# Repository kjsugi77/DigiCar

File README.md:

## 構成フォルダ
- program/        ← 車両制御プログラム（C++）
- electronics/    ← 基板データ（KiCad / Gerber / 回路図PDF）
- 3d_print/       ← 3Dプリント用データ（STL）
- parts/          ← 部品表（BOM）

---

# DigiCar（デジカー）

DigiCar は、ミニ四駆サイズの学習用自動運転ミニカーです。  
プリント基板そのものがシャーシとなる独自構造を採用し、  
RumiCar をリスペクトした教育向けプラットフォームとして開発されています。

2025年8月30日の「デジもく会」にて正式発表されました。

---

## 特徴

- プリント基板がシャーシとして機能する独自構造
- 自動運転機能を搭載予定（ToF センサ対応）
- Bluetooth をメインとした無線通信
- 教育教材としての普及を目指した低コスト設計（想定金額 約5,000円）

---

## システム構成

DigiCar は **電気系・プログラム・機械系** の 3 要素で構成されています。

### ● 電気系
- マイコン：ESP32-WROOM-32E  
- モータードライバ：TB6612FNG（東芝）  
- 電圧レギュレータ：TC1262-3.3VDB05（Microchip）  
- USBシリアル変換：FT231XS（FTDI）  
- 通信方式：Bluetooth（メイン）、Wi-Fi（サブ）

### ● プログラム
- 使用言語：C++（Arduino IDE）

### ● 機械系
- ステアリング：SG-90 サーボモータ  
- 駆動モータ：マブチ FA-130  
- ギア・シャフト・タイヤ：タミヤ製を中心に構成  
- 3Dプリント部品：ギヤケース、ステアリング機構、電池ケース固定部品など

---

## 開発ストーリー

### 2020年〜：胎動（暗黒時代）
N氏による構想が始まるも、具体化せず停滞。

### 2024年2月：運命の再始動
デジもく会で H氏の「基板、作りませんか？」の一言から再燃。

### 2025年3〜5月：継承と本格始動
京都NTで試作モックを受領し、開発が本格化。

### 2025年8〜9月：公開とコミュニティ化
初発表で手応えを掴み、はんだ付け会や Discord 開設へ。

### 2025年10〜11月：危機と復活
通信不良・異常電流の問題を発見。配線ミスを特定し、改良基板で復活。

### 2026年2月〜現在：次のステージへ
サンプル3台を提供し、マニュアル操作アプリも完成。  
現在は ToF センサ搭載による自動運転へ挑戦中。

---

## コスト構成（概算：ToF センサ除く 約 4,000 円）

### 1. 電気・電子部品（約 1,500 円）
- ESP32-WROOM-32E：約 800 円  
- FT231XS：約 320 円  
- TB6612FNG：約 200 円  
- その他：基板、抵抗・コンデンサ類

### 2. 駆動・メカ部品（約 1,000 円強）
- SG-90 サーボ：650 円  
- ギヤ・シャフト・タイヤ類：約 400 円  
- 3Dプリント部品、ネジ類

### 3. 電源（約 1,000 円強）
- エネループライト（単4×4本）：約 1,000 円  
- 電池ボックス（スイッチ付）：100 円

### 4. その他
- 基板（JLCPCB）：約 100 円

---

## ライセンス

本リポジトリは **MIT License** のもとで公開されています。

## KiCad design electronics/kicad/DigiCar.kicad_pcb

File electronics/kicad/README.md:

# kicad フォルダについて

このフォルダには、DigiCar の基板設計に使用している KiCad プロジェクトの主要ファイルが含まれています。  
回路図（schematic）と PCB レイアウト（pcb）を編集する際に使用します。

## 含まれるファイル

- **DigiCar.kicad_pro**  
  KiCad プロジェクトファイルです。  
  このファイルを開くことで、回路図エディタと PCB エディタを利用できます。

- **DigiCar.kicad_sch**  
  DigiCar の回路図データです。  
  電気的な接続、部品構成、信号ラインなどを編集できます。

- **DigiCar.kicad_pcb**  
  DigiCar の基板レイアウトデータです。  
  部品配置、配線、基板形状などを編集できます。

## 使い方

1. KiCad を起動し、**DigiCar.kicad_pro** を開きます。  
2. 回路図（Schematic Editor）または基板レイアウト（PCB Editor）を編集できます。

# About the kicad folder

This folder contains the main KiCad project files used for designing the DigiCar PCB.  
These files are used when editing the schematic and PCB layout.

## Included Files

- **DigiCar.kicad_pro**  
  The KiCad project file.  
  Opening this file allows you to access both the schematic editor and the PCB editor.

- **DigiCar.kicad_sch**  
  The schematic file for DigiCar.  
  You can edit electrical connections, component configuration, and signal lines.

- **DigiCar.kicad_pcb**  
  The PCB layout file for DigiCar.  
  You can edit component placement, routing, and the board outline.

## How to Use

1. Launch KiCad and open **DigiCar.kicad_pro**.  
2. Edit the schematic (Schematic Editor) or the PCB layout (PCB Editor) as needed.

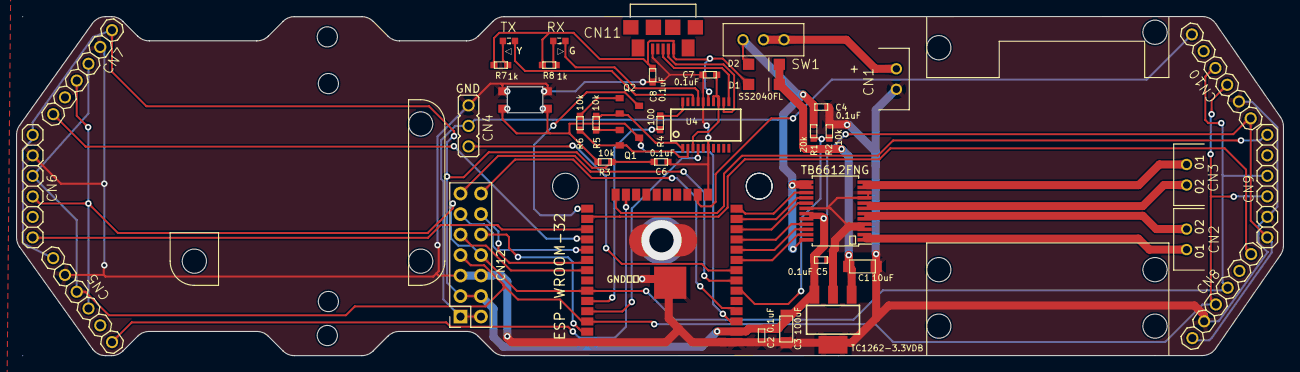
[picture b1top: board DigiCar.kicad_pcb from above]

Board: 2 copper layers, 157.0 x 42.0 mm, 40 parts (0 on the bottom side), 48 nets.

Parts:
C1: 10uF; CP3216
C2, C4, C5, C6, C7, C8: 0.1uF; CP1608
C3: 100uF; CP3216
CN1, CN2, CN3: EH-2
CN4: PINHD-1X3; CON_RC_SERVO
CN5, CN6, CN7, CN8, CN9, CN10: PINHD-1X6; 1X06
CN11: ZX62-B-5PA(11); CONN_ZX62-B-5PA(11)_HIR
CN12: Conn_02x07_Odd_Even; PinSocket_2x07_P2.54mm_Vertical
D1, D2: SS2040FL; SOD123
ESP-WROOM-32: ESP-WROOM-32
Q1, Q2: 2SC2712; SC59
R1: 20k; CP1608
R2, R3, R5, R6: 10k; CP1608
R4: 100; CP1608
R7, R8: 1k; CP1608
RX: GREEN; LED1608
SW1: SS-12SDP2; SLIDE-SW
SW2: SKRPACE010
TB6612FNG: TB6612FNG; SSOP-24_5.3x8.2mm_P0.65mm
TC1262-3.3VDB: TC1262-3.3VDB; SOT223
TX: YELLOW; LED1608
U4: FT231XS; SSOP20

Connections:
+3V3: C2.SMD1 (PIN1), C3.SMD1 (PIN1), C5.SMD1 (PIN1), C6.SMD1 (PIN1), CN5.1, CN6.1, CN7.1, CN8.1, CN9.1, CN10.1, CN12.3, CN12.4, ESP-WROOM-32.2 (3V3), R3.SMD2 (PIN2), TB6612FNG.19 (STBY), TB6612FNG.20 (VCC), TC1262-3.3VDB.3 (VO)
/BATT_CHECK: ESP-WROOM-32.6 (IO34), R1.SMD1 (PIN1), R2.SMD2 (PIN2)
/BOOT: ESP-WROOM-32.25 (IO0), Q2.C
/IO5_SS: CN12.11, ESP-WROOM-32.29 (IO5)
/IO18_SCK: CN12.12, ESP-WROOM-32.30 (IO18)
/IO19_MISO: CN12.9, ESP-WROOM-32.31 (IO19)
/IO23_MOSI: CN12.10, ESP-WROOM-32.37 (IO23)
/IO35: CN12.13, ESP-WROOM-32.7 (IO35)
/IO36: CN12.14, ESP-WROOM-32.4 (SENSOR_VP)
/MOTOR_A_IN1: ESP-WROOM-32.11 (IO26), TB6612FNG.21 (AIN1)
/MOTOR_A_IN2: ESP-WROOM-32.10 (IO25), TB6612FNG.22 (AIN2)
/MOTOR_B_IN1: ESP-WROOM-32.12 (IO27), TB6612FNG.17 (BIN1)
/MOTOR_B_IN2: ESP-WROOM-32.13 (IO14), TB6612FNG.16 (BIN2)
/MOTOR_PWM_A: ESP-WROOM-32.9 (IO33), TB6612FNG.23 (PWMA)
/MOTOR_PWM_B: ESP-WROOM-32.14 (IO12), TB6612FNG.15 (PWMB)
/RESET: ESP-WROOM-32.3 (EN), Q1.C, R3.SMD1 (PIN1), SW2.1, SW2.2
/RXD: ESP-WROOM-32.34 (RXD0), R4.SMD2 (PIN2)
/RX_LED: RX.C, U4.17 (CBUS1)
/SCL: CN5.3, CN6.3, CN7.3, CN8.3, CN9.3, CN10.3, CN12.7, ESP-WROOM-32.36 (IO22)
/SDA: CN5.4, CN6.4, CN7.4, CN8.4, CN9.4, CN10.4, CN12.8, ESP-WROOM-32.33 (IO21)
/SERVO_PWM: CN4.1, ESP-WROOM-32.8 (IO32)
/TOF_SHDN0: CN5.6, ESP-WROOM-32.23 (IO15)
/TOF_SHDN1: CN6.6, ESP-WROOM-32.27 (IO16)
/TOF_SHDN2: CN7.6, ESP-WROOM-32.28 (IO17)
/TOF_SHDN3: CN8.6, ESP-WROOM-32.26 (IO4)
/TOF_SHDN4: CN9.6, ESP-WROOM-32.24 (IO2)
/TOF_SHDN5: CN10.6, ESP-WROOM-32.16 (IO13)
/TXD: ESP-WROOM-32.35 (TXD0), U4.4 (RXD)
/TX_LED: TX.C, U4.18 (CBUS0)
GND: C1.SMD2 (PIN2), C2.SMD2 (PIN2), C3.SMD2 (PIN2), C4.SMD2 (PIN2), C5.SMD2 (PIN2), C6.SMD2 (PIN2), C7.SMD2 (PIN2), C8.SMD2 (PIN2), CN1.2, CN4.3, CN5.2, CN6.2, CN7.2, CN8.2, CN9.2, CN10.2, CN11.5, CN12.5, CN12.6, ESP-WROOM-32.1 (GND@1), ESP-WROOM-32.15 (GND@2), ESP-WROOM-32.38 (GND@3), ESP-WROOM-32.GND (GND@4), R2.SMD1 (PIN1), SW2.3, SW2.4, TB6612FNG.3 (PGND1), TB6612FNG.4 (PGND1), TB6612FNG.9 (PGND2), TB6612FNG.10 (PGND2), TB6612FNG.18 (GND), TC1262-3.3VDB.2 (GND), TC1262-3.3VDB.4 (GND), U4.6 (GND@6), U4.16 (GND@16)
unnamed: C1.SMD1 (PIN1), D1.C, D2.C, TC1262-3.3VDB.1 (VI)
unnamed: C7.SMD1 (PIN1), U4.3 (VCCIO), U4.13 (3V3OUT), U4.14 (~RESET)
unnamed: CN2.1, TB6612FNG.1 (AO1), TB6612FNG.2 (AO1)
unnamed: CN2.2, TB6612FNG.5 (AO2), TB6612FNG.6 (AO2)
unnamed: CN3.1, TB6612FNG.7 (BO2), TB6612FNG.8 (BO2)
unnamed: CN3.2, TB6612FNG.11 (BO1), TB6612FNG.12 (BO1)
unnamed: R4.SMD1 (PIN1), U4.20 (TXD)
unnamed: Q2.E, R5.SMD1 (PIN1), U4.1 (~DTR)
unnamed: Q1.B, R5.SMD2 (PIN2)
unnamed: Q1.E, R6.SMD1 (PIN1), U4.2 (~RTS)
unnamed: Q2.B, R6.SMD2 (PIN2)
unnamed: R7.SMD1 (PIN1), TX.A
unnamed: R8.SMD1 (PIN1), RX.A
unnamed: CN1.1, SW1.2, SW1.3 (S)
unnamed: CN11.2, U4.12 (USBDM)
unnamed: CN11.3, U4.11 (USBDP)
VBUS: C8.SMD1 (PIN1), CN11.1, D1.A, R7.SMD2 (PIN2), R8.SMD2 (PIN2), U4.15 (VCC)
V_BATT: C4.SMD1 (PIN1), CN4.2, CN12.1, CN12.2, D2.A, R1.SMD2 (PIN2), SW1.1 (O), TB6612FNG.13 (VM2), TB6612FNG.14 (VM3), TB6612FNG.24 (VM1)

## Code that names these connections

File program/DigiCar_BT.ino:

#include "BluetoothSerial.h"

#if !defined(CONFIG_BT_ENABLED) || !defined(CONFIG_BLUEDROID_ENABLED)
#error Bluetooth is not enabled! Please run `make menuconfig` to and enable it
#endif

// デバッグ出力の制御
#define DEBUG_SERIAL 1  // 0: 無効化、1: 有効化

// モーター制御ピン（TB6612FNG）
#define MOTOR_A_IN1  26  // GPIO26
#define MOTOR_A_IN2  25  // GPIO25
#define MOTOR_A_PWM  33  // GPIO33
#define MOTOR_B_IN1  27  // GPIO27
#define MOTOR_B_IN2  14  // GPIO14
#define MOTOR_B_PWM  12  // GPIO12

// サーボモーター制御ピン（ステアリング）
#define SERVO_PIN    32  // GPIO32

// Bluetooth設定
BluetoothSerial SerialBT;
const char* deviceName = "DigiCar_Control";

void setup() {
  Serial.begin(115200);
  #if DEBUG_SERIAL
  Serial.println("=== DigiCar Steering Control (Simple) ===");
  #endif
  
  // CPU周波数を下げて発熱を軽減
  setCpuFrequencyMhz(80);
  #if DEBUG_SERIAL
  Serial.print("CPU Frequency: ");
  Serial.print(getCpuFrequencyMhz());
  Serial.println(" MHz");
  #endif
  
  // モーター制御ピンの設定
  pinMode(MOTOR_A_IN1, OUTPUT);
  pinMode(MOTOR_A_IN2, OUTPUT);
  pinMode(MOTOR_A_PWM, OUTPUT);
  pinMode(MOTOR_B_IN1, OUTPUT);
  pinMode(MOTOR_B_IN2, OUTPUT);
  pinMode(MOTOR_B_PWM, OUTPUT);
  
  // サーボピンの設定
  pinMode(SERVO_PIN, OUTPUT);
  
  // 初期状態：停止
  stopMotors();
  setServoAngle(90); // サーボを中央位置に
  #if DEBUG_SERIAL
  Serial.println("Motors and Steering initialized");
  #endif
  
  // Bluetooth起動
  SerialBT.begin(deviceName);
  #if DEBUG_SERIAL
  Serial.println("Bluetooth started");
  Serial.print("Device Name: ");
  Serial.println(deviceName);
  Serial.println("Commands: F<speed>, B<speed>, S, T<angle>, J<speed>,<steering>,<direction>");
  #endif
}

void loop() {
  // Bluetooth通信を処理
  if (SerialBT.available()) {
    String command = SerialBT.readStringUntil('\n');
    command.trim(); // 前後の空白文字（スペース、タブ、改行など）を削除
    
    #if DEBUG_SERIAL
    Serial.print("Received: ");
    Serial.println(command);
    #endif
    
    parseCommand(command); // コマンドを解析して実行
  }
  
  // サーボ制御を非同期で実行
  updateServoAsync();
  
  yield();
}

// サーボ角度設定関数（ステアリング）- 非ブロッキング方式
static int currentServoAngle = 90;

void setServoAngle(int angle) {
  // 角度を60～120度の範囲に制限
  if (angle < 60) angle = 60;
  if (angle > 120) angle = 120;
  currentServoAngle = angle;
}

// サーボ制御を非同期で実行（非ブロッキング方式）
// 20msごとにパルスを送信して、Bluetooth通信をブロックしない
void updateServoAsync() {
  static unsigned long lastPulse = 0;
  unsigned long now = millis();
  
  // 20msごとにパルスを送信（50Hz）
  if (now - lastPulse >= 20) {
    lastPulse = now;
    // 角度をパルス幅に変換（0度=500us, 180度=2500us）
    int pulseWidth = map(currentServoAngle, 0, 180, 500, 2500);
    digitalWrite(SERVO_PIN, HIGH);
    delayMicroseconds(pulseWidth);
    digitalWrite(SERVO_PIN, LOW);
  }
}

// Bluetoothコマンド解析関数
// コマンド形式: F<speed>, B<speed>, S, T<angle>, J<speed>,<steering>,<direction>
void parseCommand(String command) {
  if (command.length() == 0) return;
  
  char cmd = command.charAt(0);
  
  if (cmd == 'F' || cmd == 'f') {
    // 前進: F<speed> (例: F50 = 50%速度で前進)
    int speed = command.substring(1).toInt();
    if (speed > 0 && speed <= 100) {
      moveForwardWithSpeed(speed);
      #if DEBUG_SERIAL
      Serial.print("Forward: ");
      Serial.println(speed);
      #endif
    }
  } else if (cmd == 'B' || cmd == 'b') {
    // 後退: B<speed> (例: B50 = 50%速度で後退)
    int speed = command.substring(1).toInt();
    if (speed > 0 && speed <= 100) {
      moveBackwardWithSpeed(speed);
      #if DEBUG_SERIAL
      Serial.print("Backward: ");
      Serial.println(speed);
      #endif
    }
  } else if (cmd == 'S' || cmd == 's') {
    // 停止: S
    stopMotors();
    #if DEBUG_SERIAL
    Serial.println("Stop");
    #endif
  } else if (cmd == 'T' || cmd == 't') {
    // ステアリング: T<angle> (例: T90 = 中央, T60 = 左端, T120 = 右端)
    int angle = command.substring(1).toInt();
    if (angle >= 60 && angle <= 120) {
      setServoAngle(angle);
      #if DEBUG_SERIAL
      Serial.print("Steering: ");
      Serial.println(angle);
      #endif
    }
  } else if (cmd == 'J' || cmd == 'j') {
    // ジョイスティック: J<speed>,<steering>,<direction>
    // 例: J50,90,前進 = 速度50%, ステアリング90度, 前進方向
    int firstComma = command.indexOf(',');
    int secondComma = command.indexOf(',', firstComma + 1);
    
    if (firstComma > 0 && secondComma > firstComma) {
      int speed = command.substring(1, firstComma).toInt();
      int steering = command.substring(firstComma + 1, secondComma).toInt();
      String direction = command.substring(secondComma + 1);
      
      if (steering >= 60 && steering <= 120) {
        setServoAngle(steering);
      }
      
      if (speed > 5) {
        if (direction == "前進" || direction == "forward" || direction == "F") {
          moveForwardWithSpeed(speed);
        } else if (direction == "後進" || direction == "backward" || direction == "B") {
          moveBackwardWithSpeed(speed);
        } else {
          moveForwardWithSpeed(speed); // デフォルトは前進
        }
      } else {
        stopMotors();
      }
      
      #if DEBUG_SERIAL
      Serial.print("Joystick: speed=");
      Serial.print(speed);
      Serial.print(", steering=");
      Serial.print(steering);
      Serial.print(", direction=");
      Serial.println(direction);
      #endif
    }
  }
  
  SerialBT.println("OK");
}

// モーター制御関数（PWM速度制御）
void moveForwardWithSpeed(int speedPercent) {
  // 速度をPWM値に変換（0-100% → 0-255）
  int pwmValue = map(speedPercent, 0, 100, 0, 255);
  
  // Motor A: 前進
  digitalWrite(MOTOR_A_IN1, HIGH);
  digitalWrite(MOTOR_A_IN2, LOW);
  analogWrite(MOTOR_A_PWM, pwmValue);
  
  // Motor B: 前進
  digitalWrite(MOTOR_B_IN1, HIGH);
  digitalWrite(MOTOR_B_IN2, LOW);
  analogWrite(MOTOR_B_PWM, pwmValue);
  
  yield();
}

void moveBackwardWithSpeed(int speedPercent) {
  // 速度をPWM値に変換（0-100% → 0-255）
  int pwmValue = map(speedPercent, 0, 100, 0, 255);
  
  // Motor A: 後退
  digitalWrite(MOTOR_A_IN1, LOW);
  digitalWrite(MOTOR_A_IN2, HIGH);
  analogWrite(MOTOR_A_PWM, pwmValue);
  
  // Motor B: 後退
  digitalWrite(MOTOR_B_IN1, LOW);
  digitalWrite(MOTOR_B_IN2, HIGH);
  analogWrite(MOTOR_B_PWM, pwmValue);
  
  yield();
}

void stopMotors() {
  #if DEBUG_SERIAL
  Serial.println("Stop motors");
  #endif
  
  digitalWrite(MOTOR_A_IN1, LOW);
  digitalWrite(MOTOR_A_IN2, LOW);
  analogWrite(MOTOR_A_PWM, 0);
  
  digitalWrite(MOTOR_B_IN1, LOW);
  digitalWrite(MOTOR_B_IN2, LOW);
  analogWrite(MOTOR_B_PWM, 0);
}

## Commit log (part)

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2026-03-14 Update DigiCar-VirtualStick
    AP-SSIDをMACアドレス下4桁で個別化
    （複数デバイスの同時運転対応）
    起動時に個別AP-SSIDをシリアル表示
    ボタンイベント修正＋テキスト選択防止
    速度スライダーをリアルタイム適用
    ジョイスティックのオフセット修正
2026-05-31 Rename 20250726 DigiCar_Steering_Control_Slider.ino to program/20250726 DigiCar_Steering_Control_Slider.ino
2026-05-31 Rename 20250915 DigiCar_Steering_Control_VirtualStick.ino to program/20250915 DigiCar_Steering_Control_VirtualStick.ino
2026-05-31 Rename 20251206 DigiCar_BT.ino to program/20251206 DigiCar_BT.ino
2026-05-31 Rename 20251206_APP_DEVELOPER_GUIDE.md to program/20251206_APP_DEVELOPER_GUIDE.md
2026-05-31 Rename 20250915 DigiCar_Steering_Control_VirtualStick.ino to DigiCar_WiFi.ino
2026-05-31 Rename 20251206 DigiCar_BT.ino to DigiCar_BT.ino
2026-05-31 Rename 20251206_APP_DEVELOPER_GUIDE.md to DigiCar_BT_APP_DEVELOPER_GUIDE.md
